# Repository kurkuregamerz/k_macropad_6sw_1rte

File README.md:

# K_MACROPAD_6SW_1RTE
6 key macropad with a rotary encoder.

This is a project for hackclub stardance.
# Features
- EC11 Rotary Encoder for volume up and down
- Has 6 Cherry MX Mechanical keys
- Snap_fit_case
# Firmware
- QMK
# Gallery

- Assembled Macropad

- Top Case

- Bottom Case

- PCB

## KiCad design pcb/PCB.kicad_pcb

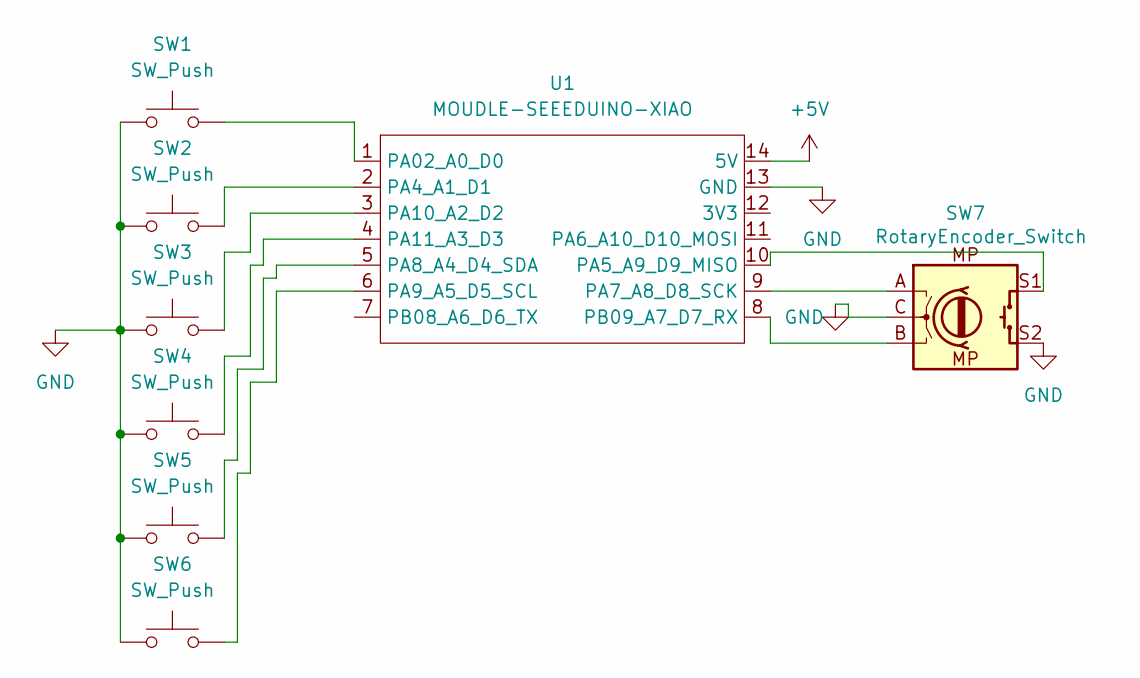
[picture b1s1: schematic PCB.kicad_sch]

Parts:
SW1: SW_Push; SW_Cherry_MX_1.00u_Plate
SW2, SW3, SW4, SW5, SW6: SW_Push; SW_Cherry_MX_1.00u_PCB
SW7: RotaryEncoder_Switch; RotaryEncoder_Alps_EC12E-Switch_Vertical_H20mm
U1: MOUDLE-SEEEDUINO-XIAO; XIAO-Generic-Hybrid-14P-2.54-21X17.8MM

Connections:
+5V: U1.14 (5V)
GND: SW1.1, SW2.1, SW3.1, SW4.1, SW5.1, SW6.1, SW7.C, SW7.S2, U1.13 (GND)
unnamed: SW1.2, U1.1 (PA02_A0_D0)
unnamed: SW2.2, U1.2 (PA4_A1_D1)
unnamed: SW7.S1, U1.10 (PA5_A9_D9_MISO)
unnamed: SW7.A, U1.9 (PA7_A8_D8_SCK)
unnamed: SW5.2, U1.5 (PA8_A4_D4_SDA)
unnamed: SW6.2, U1.6 (PA9_A5_D5_SCL)
unnamed: SW3.2, U1.3 (PA10_A2_D2)
unnamed: SW4.2, U1.4 (PA11_A3_D3)
unnamed: SW7.B, U1.8 (PB09_A7_D7_RX)

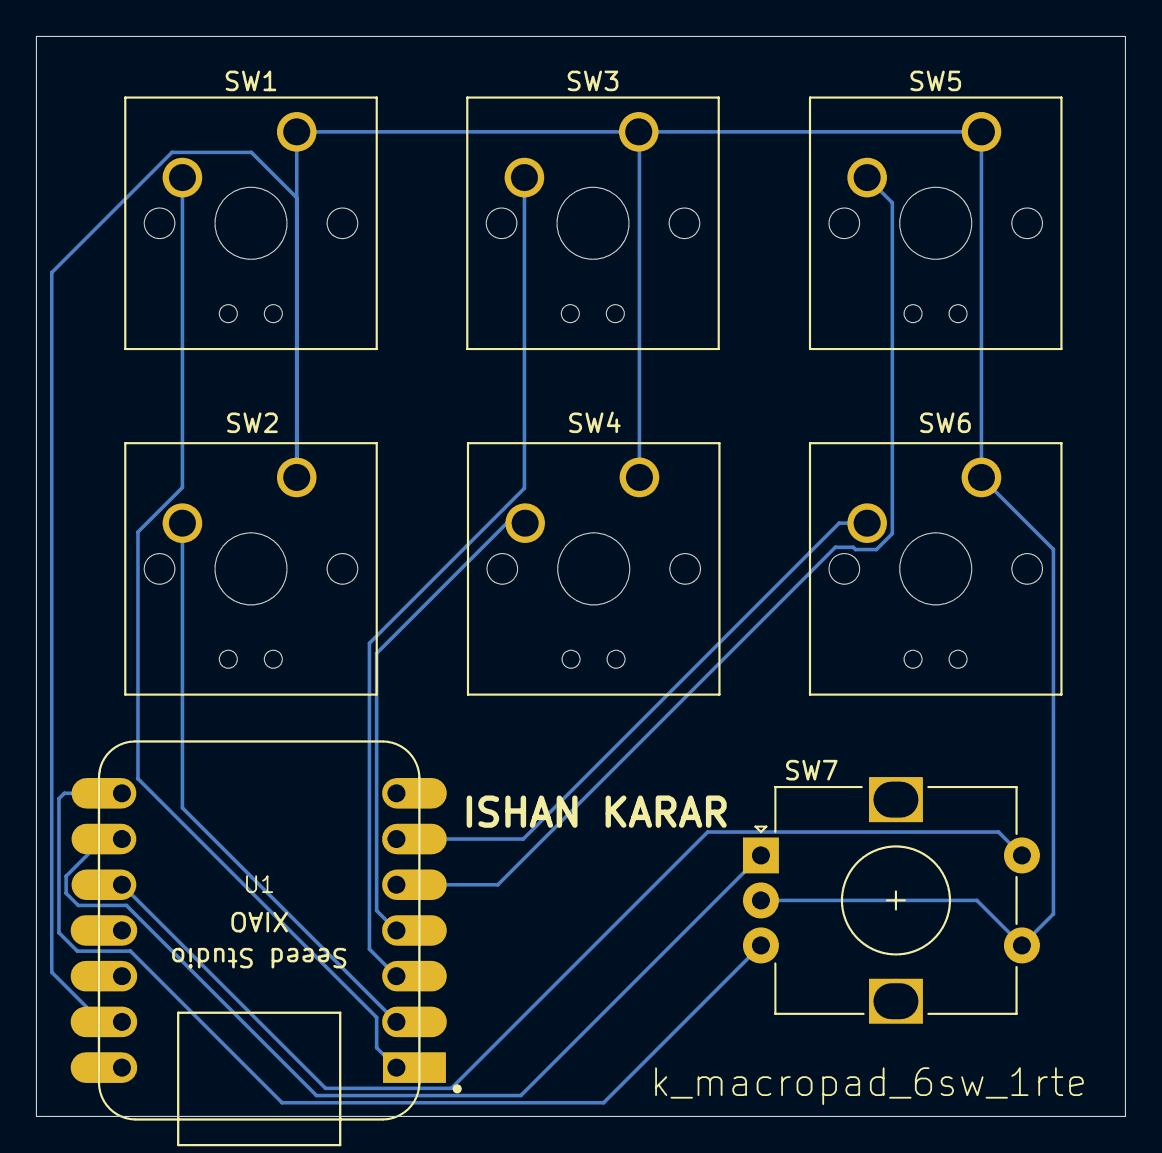
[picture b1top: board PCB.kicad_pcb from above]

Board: 2 copper layers, 60.5 x 60.0 mm, 8 parts (0 on the bottom side), 10 nets.
